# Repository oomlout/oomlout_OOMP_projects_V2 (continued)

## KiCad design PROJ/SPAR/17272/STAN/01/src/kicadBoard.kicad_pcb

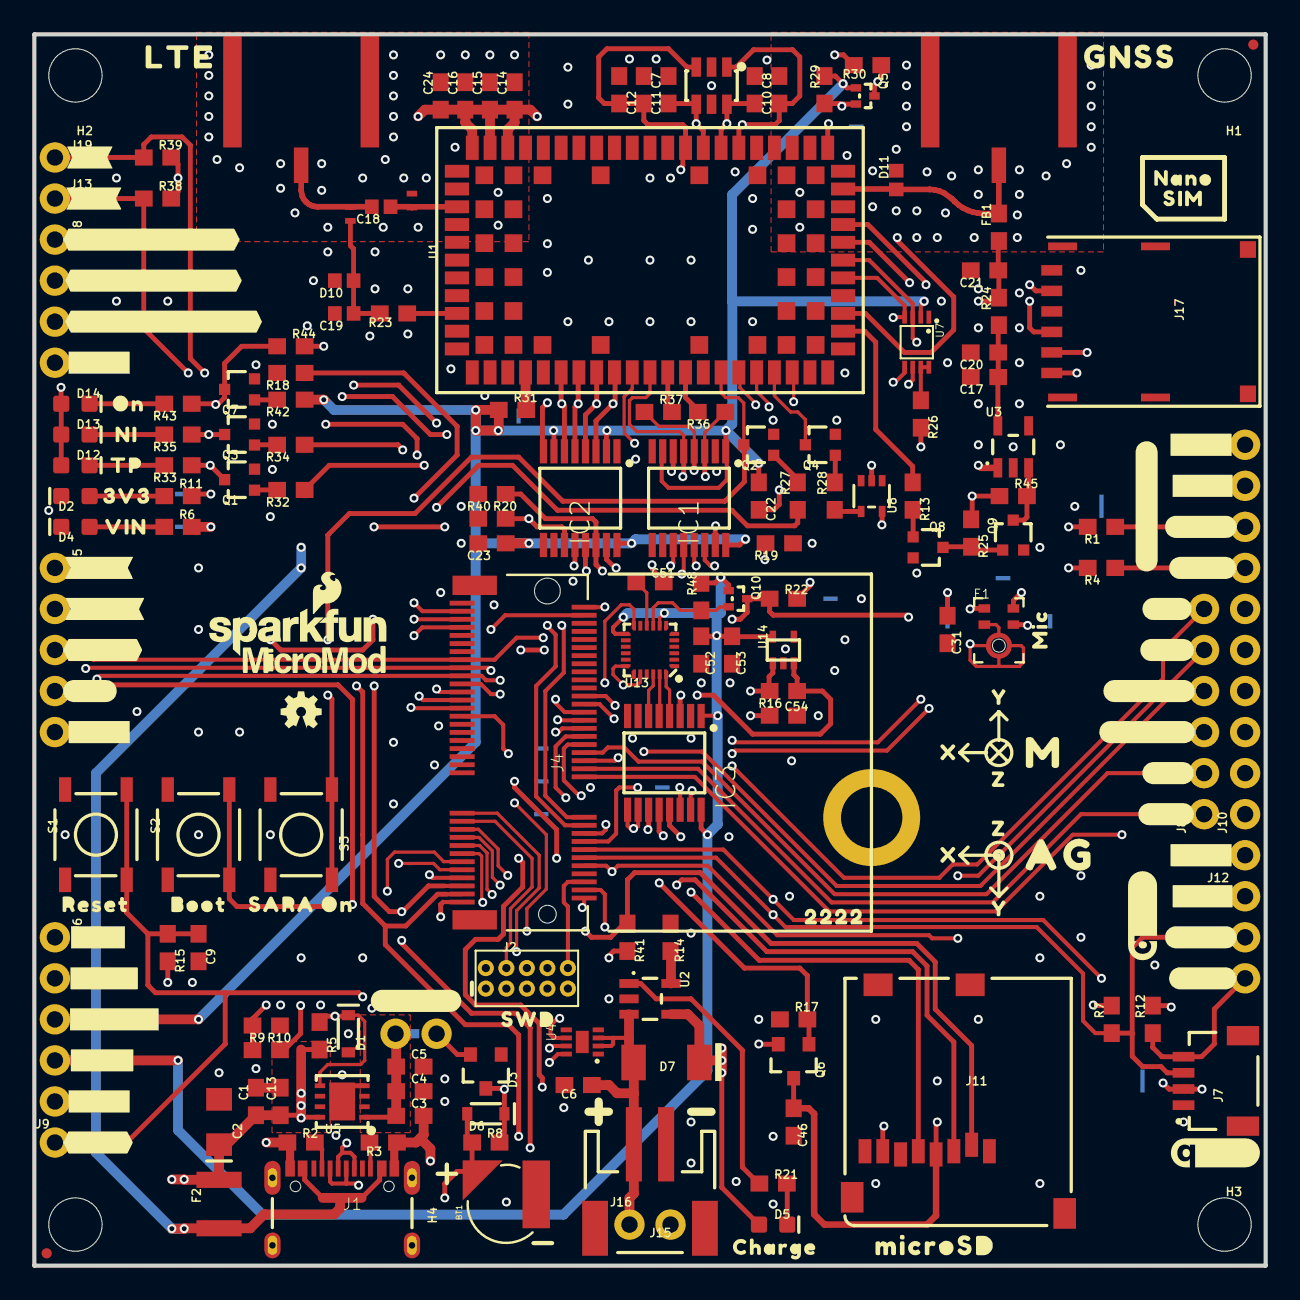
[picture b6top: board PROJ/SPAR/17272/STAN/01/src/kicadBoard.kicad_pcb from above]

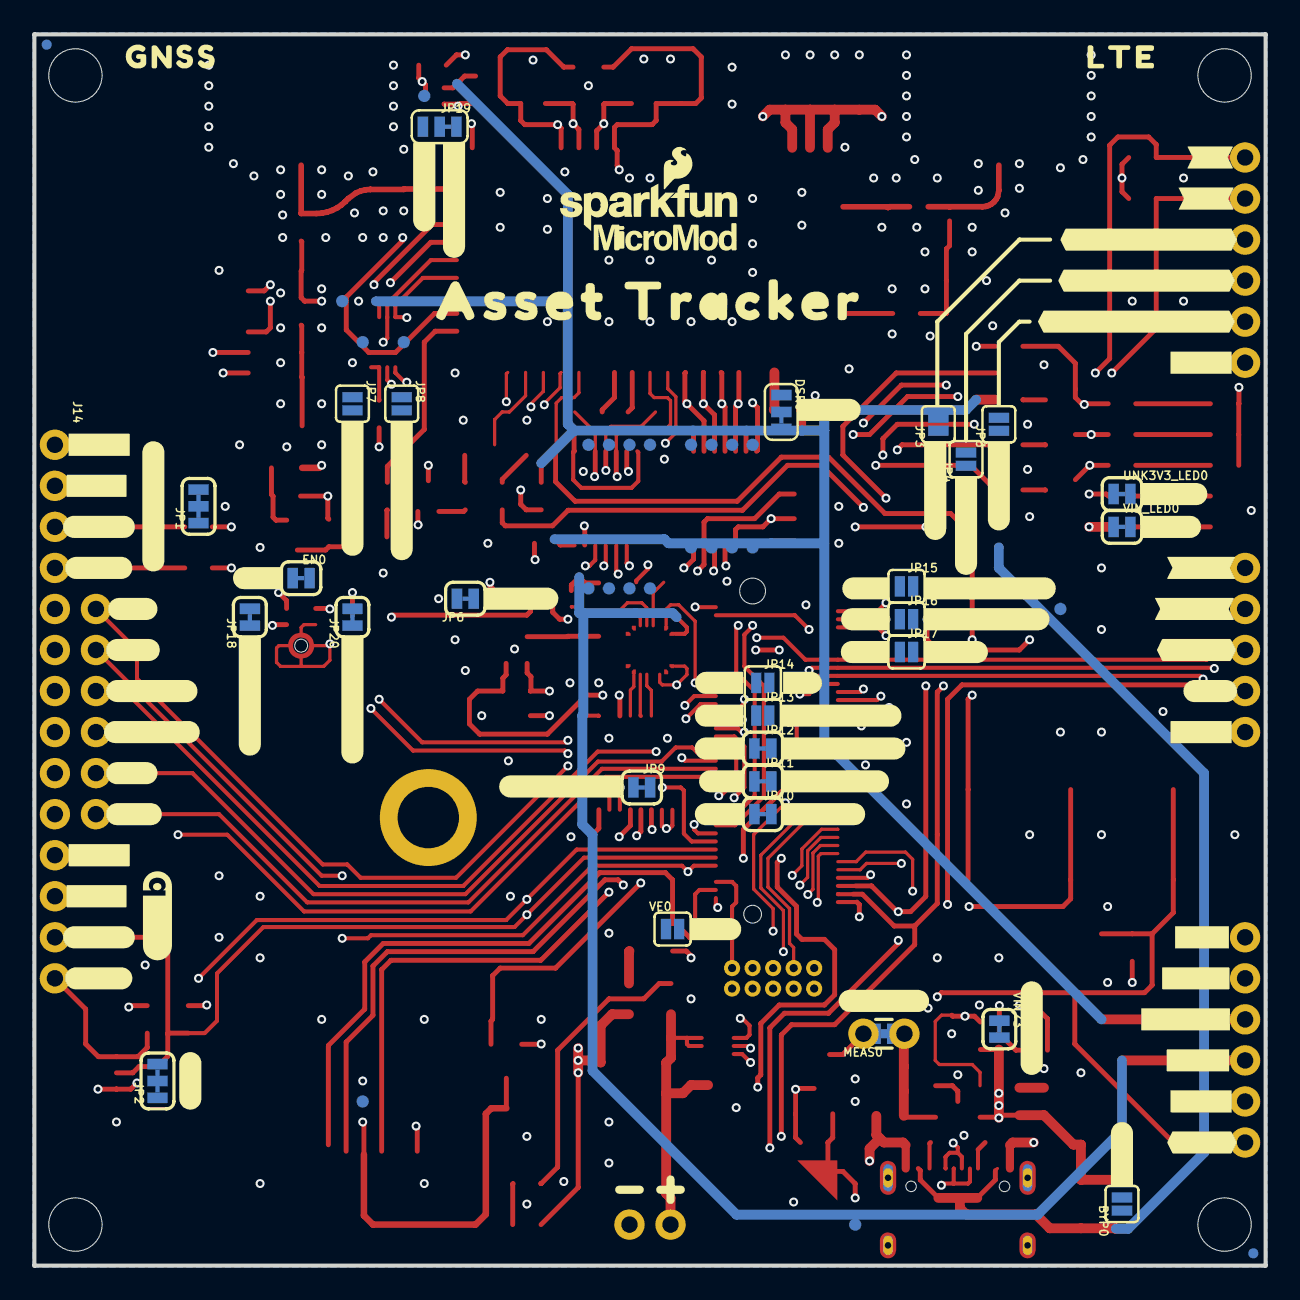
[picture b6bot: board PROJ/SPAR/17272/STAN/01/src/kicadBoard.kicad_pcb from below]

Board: 4 copper layers, 76.2 x 76.2 mm, 340 parts (128 on the bottom side), 137 nets.

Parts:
BT1: ML414H; ML414H_IV01E
BYP0: JUMPER-SMT_2_NO_SILK; SMT-JUMPER_2_NO_SILK
C1, C4, C12, C14, C20, C22, C23, C31, C46, C51, C52: 0.1uF; 0603
C2: 10uF; EIA3216
C3, C6: 4.7uF; 0603
C5, C13: 0.22uF; 0603
C7, C8, C10, C11, C21: 47pF; 0603
C9: 1nF; 0603
C15: 68pF; 0603
C16: 10uF; 0603
C17, C53, C54: 1.0uF; 0603
C18: 33pF; 0402
C19: 27pF; 0402
C24: 15pF; 0603
D1: 3.3V; SOD-323
D2: RED; LED-0603
D3: BAS70-05; SOT23-3
D4, D5: Yellow; LED-0603
D6: 3A/10V/280mV; SOD-323
D7: 1A/15V/220mV; DO-214BA
D8: DT1042-04SO-7; SOT23-6L
D10, D11: PESD0402; 0402
D12: GREEN; LED-0603
D13: BLUE; LED-0603
D14: WHITE; LED-0603
DSR0: JUMPER-SMT_3_1-NC_TRACE_SILK; SMT-JUMPER_3_1-NC_TRACE_SILK
E1: SPH0641LM4H-1; SPH0641LM4H-1_MICROPHONE
E3, E4: ANTENNA-SMA-GROUNDEDEDGE_SMA_SMD; SMA-EDGE-SMD
EN0: SMT-JUMPER_2_NC_TRACE_SILK
F2: 6V/2A; 1210
FB1: 30Ω/1.8A; 0603
FD1, FD2, FD3, FD4: FIDUCIALUFIDUCIAL; FIDUCIAL-MICRO
FRAME1, FRAME2: FRAME-LEDGER; CREATIVE_COMMONS
H1, H2, H3, H4: STAND-OFF
H5: STAND-OFF-REFLOW2.5MM_TALL; STAND-OFF-REFLOW-M2.5
IC1, IC2, IC3: SN74AVC4T774PW; SOP65P640X120-16N
J1: USB-C-16P_4LAYER-PADS
J2: JTAG; 2X5-PTH-1.27MM
J4: MICROMOD-2222-C; M.2-CONNECTOR-E
J5: SPI; 1X05_NO_SILK
J6: DIAG; 1X05_NO_SILK
J7: QWIIC_RIGHT_ANGLE; JST04_1MM_RA
J8, J10: 1X06_NO_SILK
J9: !RST!; 1X01_NO_SILK
J11: microSD; MICRO-SD-SOCKET
J12, J14: 1X04_NO_SILK
J13: TP; 1X01_NO_SILK
J15: JST-2-SMD
J16: 1X02_NO_SILK
J17: NANO_SIM; NANO_SIM_WURTH_693043020611
J18: SARA_USB; 1X04_NO_SILK
J19: NI; 1X01_NO_SILK
JP1, JP2: SMT-JUMPER_3_2-NC_TRACE_SILK
JP3, JP4, JP5, JP7, JP8, JP13, JP14, JP15, JP16, JP17: JUMPER-SMT_2_NO_SILK; SMT-JUMPER_2_NO_SILK
JP6, JP9, JP10, JP11, JP12, JP18, JP20: JUMPER-SMT_2_NC_TRACE_SILK; SMT-JUMPER_2_NC_TRACE_SILK
JP19: JUMPER-SMT_3_1-NC_TRACE_SILK; SMT-JUMPER_3_1-NC_TRACE_SILK
L1: DNP; 0402_COILCRAFT
L2: 68nH; 0402_COILCRAFT
LOGO1, LOGO4: SFE_LOGO_NAME_FLAME.1_INCH; SFE_LOGO_NAME_FLAME_.1
LOGO2, LOGO6, LOGO7: QWIIC_LOGO_CONNECTOR; QWIIC_5.5MM
LOGO3: OSHW-LOGOMINI; OSHW-LOGO-MINI
LOGO5: SPECIAL_INSTRUCTIONS-ORDERING; ORDERING_INSTRUCTIONS
MEAS0: COMBO-JUMPER_2_NC_TRACE
Q1, Q2, Q3, Q4, Q7, Q8, Q9: 310mA/60V/1.6Ω; SOT323
Q5, Q10: 20V/0.2A/8MHz/1.2Ω/1Vth; SOT-416FL
Q6: 20V/4.2A/52mΩ/1.4W; SOT23-3
R1, R4, R7, R12, R14, R22, R29, R30, R48: 2.2k; 0603
R2, R3: 5.1k; 0603
R5, R15, R16, R17, R18, R19, R20, R25, R38, R39, R40, R41, R44, R45: 100k; 0603
R6: 4.7k; 0603
R8: 3.3k; 0603
R9, R23: 10k; 0603
R10: 20k; 0603
R11, R13, R21, R27, R28, R32, R34, R42, R43: 1k; 0603
R24: 10; 0603
R26: 200k; 0603
R31, R36, R37: 0; 0603
R33: 100; 0603
R35: 470; 0603
S1: RESET; TACTILE_SWITCH_SMD_5.2MM
S2: BOOT; TACTILE_SWITCH_SMD_5.2MM
S3: SARA_PWR; TACTILE_SWITCH_SMD_5.2MM
TP1, TP2, TP3, TP4, TP5, TP6, TP7, TP8, TP9, TP10, TP12, TP13, TP14, TP15, TP16, TP17, TP18, TP19, TP20, TP21, TP22, TP23, TP24: TEST-POINT3; PAD.03X.03
U1: SARA-R510M8S; SARA-LGA
U2: MCP73831; SOT23-5
U3: 3.3V; SOT23-5
U4: MAX17048; DFN-8
U5: AP7361C-33FGE; UDFN-8
U7: PCA9306; VSSOP_8PIN
U8: 74HC1G04; SOT353
U13: 9DoF IMU; QFN24-3X3-ICM-20948
U14: 1.8V/100mA; SC70
U$1: #EN#0
U$2: MIC0
U$3, U$11, U$13, U$14: #3V3#1
U$4: #3V3#0
U$5, U$23: #SARA_I�C#0
U$6, U$7: #A0#5
U$8, U$9: #A1#4
U$10, U$25, U$35, U$68: #D0#1
U$12, U$15, U$16, U$22: #GND#0
U$17, U$86: #RST#1
U$18: #VE#0
U$19, U$87: #MEAS#2
U$20: #VIN#1
U$21: SWD0
U$24, U$34: MICROMOD_LOGO_.35
U$26, U$27, U$43, U$44: #SCL#3
U$28: MICROSD0
U$29, U$31: #D1#0
U$30, U$37, U$50, U$51: #SDA#2
U$32, U$41: #PWM0#3
U$33: #BYP#1
U$36: 3V37
U$38, U$48: Y2
U$39, U$47: X1
U$40: BOOT5
U$42, U$49: #PWM1#2
U$45: RESET6
U$46: VIN8
U$52, U$54: Z0
U$53: #I�C#0
U$55, U$56, U$73, U$74, U$81, U$82: #GND#4
U$57, U$58: #TP#0
U$59, U$60: #NI#0
U$61, U$62, U$63, U$64: #SARA_USB_D##0
U$65, U$66: #SARA_USB_DET#0
U$67, U$75: #VIN#0
U$69, U$70: #CIPO#2
U$71, U$72: #COPI#1
U$76, U$79: #3#3V#0
U$77, U$78: #SCK#0
U$80, U$83: #VCCIO#0
U$84, U$85: #1#8V#0
U$88, U$89: LTE0
U$90: NI0
U$91: TP0
U$92, U$93: #USB_D##0
U$94: #V_USB#0
U$95: AG0
U$96: M0
U$97: CHARGE0
U$98: ASSET_TRACKER0
U$99, U$100: GNSS0
U$101: ON0
U$102, U$105: #DSR#0
U$103: #SARA_INT#0
U$104: #RI#0
U$106: #SD_#CS##0
U$107: #IMU_PWR#0
U$108: #LTE_PWR#0
U$109: #SD_PWR#0
U$110: #SARA_#ON##0
U$111: #SARA_SCL#0
U$112: #SARA_SDA#0
U$113: SARA_ON0
U$114: #CIPO#0
U$115: 22220
U$116: #PDM_CLK#0
U$117: #PDM_DAT#0
U$118: #EXT_INT#0
U$119: #GPIO3#0
U$122: #G0#0
U$123: #G1#0
U$124: #G2#0
U$125: #G3#0
U$126: #G4#0
U$127: #G7#0
U$128: #G6#0
U$129: #G5#0
U$130: NANO0
U$131: SIM0
U$133: #VIN#3#0
U$134: #ICM_INT#0
UNK3V3_LED0: SMT-JUMPER_2_NC_TRACE_SILK
VE0: SMT-JUMPER_2_NO_SILK
VIN/3: JUMPER-SMT_2_NC_TRACE_SILK; SMT-JUMPER_2_NC_TRACE_SILK
VIN_LED0: SMT-JUMPER_2_NC_TRACE_SILK

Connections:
1.8V: C52.1, C53.1, IC3.1, IC3.16, J6.4, Q10.1, R48.2, U13.8, U13.13, U14.5
3.3V: C14.1, C15.1, C16.1, C24.1, C31.1, C54.1, D3.2, D12.A, D13.A, D14.A, EN0.2, IC1.15, IC2.15, IC3.15, J2.1, J4.2, J4.74, J6.2, J7.2, J12.2, J14.2, JP1.2, JP2.2, JP6.2, MEAS0.2, MEAS0.4, Q6.2, R15.2, R16.2, R25.1, R26.2, R30.2, R38.2, R39.2, R41.2, R44.2, R45.1, U1.51, U1.52, U1.53, U8.5, U14.1, UNK3V3_LED0.2
3.3V_EN: J4.4, VE0.1
A0: J4.34, J8.1
A1: J4.38, J8.2
ANT_GNSS_PWR_EN: R13.1, U1.23
ANT_REG_EN: Q9.3, R45.2, U3.3
CHG_LED: R21.1, U2.1
CTS1: IC1.12, J4.15, TP7.P$1
D0: J4.10, J5.4, J8.5
D1: J4.18, J8.6
DCD: IC2.13, J4.20, TP19.P$1
DSR: IC2.11, JP17.2, R20.2, TP21.P$1
DTR: IC2.14, J4.22, R40.1, TP18.P$1
G0: J4.40, JP10.1
G1: J4.42, JP11.1
G2: J4.44, JP12.1
G3: J4.46, JP13.1
G4: J4.48, JP14.1
G5: J4.73, JP15.1
G6: J4.71, JP16.1
G7: J4.69, JP17.1
GND: BT1.-, C1.2, C2.-, C3.2, C4.2, C5.2, C6.2, C7.2, C8.2, C9.2, C10.1, C11.1, C12.1, C13.2, C14.2, C15.2, C16.2, C17.2, C19.2, C20.2, C21.2, C22.2, C23.2, C24.2, C31.2, C46.2, C51.2, C52.2, C53.2, C54.2, D1.A, D2.C, D4.C, D8.2, D8.5, D10.2, D11.2, DSR0.1, E1.2, E1.3, E1.6, E1.7, E1.8, E3.GND@0, E3.GND@1, E4.GND@0, E4.GND@1, H5.1, IC1.2, IC1.8, IC1.9, IC1.10, IC2.1, IC2.9, IC2.10, IC3.2, IC3.7, IC3.8, IC3.9, IC3.10, J1.GND, J1.GND2, J2.3, J2.5, J2.9, J4.1, J4.7, J4.33, J4.36, J4.39, J4.45, J4.75, J5.5, J6.5, J7.1, J10.1, J10.2, J10.3, J10.4, J10.5, J10.6, J11.CD1, J11.GND, J11.GND1, J11.GND3, J12.1, J14.1, J15.1, J16.2, J17.C5, J18.4, L1.P$2, Q1.2, Q2.2, Q3.2, Q4.2, Q7.2, Q8.2, Q9.2, R2.1, R3.1, R9.1, R14.1, R17.1, R18.2, R19.1, R20.1, R40.2, S1.1, S1.2, S2.1, S2.2, S3.3, S3.4, U1.1, U1.3, U1.5, U1.14, U1.20, U1.21, U1.22, U1.30, U1.32, U1.43, U1.50, U1.54, U1.55, U1.57, U1.58, U1.59, U1.60, U1.61, U1.63, U1.64, U1.65, U1.66, U1.67, U1.68, U1.69, U1.70, U1.71, U1.72, U1.73, U1.74, U1.75, U1.76, U1.77, U1.78, U1.79, U1.80, U1.81, U1.82, U1.83, U1.84, U1.85, U1.86, U1.87, U1.88, U1.89, U1.90, U1.91, U1.92, U1.93, U1.94, U1.95, U1.96, U2.2, U3.2, U4.1, U4.4, U4.6, U4.9, U5.4, U5.EP, U7.P1, U8.3, U13.18, U13.20, U14.2
I2C_SCL: J4.14, J7.4, J12.4, R12.1, U4.7
I2C_SDA: J4.12, J7.3, J12.3, R7.1, U4.8
I2S_SCK/PDM_CLK: E1.4, JP18.2
I2S_WS/PDM_DAT: E1.1, JP20.2
ICM-20948-LV_INT: IC3.3, U13.12
ICM-20948-LV_SCK: IC3.5, U13.23
ICM-20948-LV_SDI: IC3.4, U13.24
ICM-20948-LV_SDO: Q10.2, R48.1, U13.9
ICM-20948-LV_~CS: IC3.6, U13.22
ICM_INT: IC3.14, JP9.1
ICM_PWR: JP13.2, R16.1, U14.3
ICM_~CS: IC3.11, J4.55
LTE_PWR_ON: JP12.2, R18.1, R27.1
MICROSD_PWR: JP11.2, Q6.1, R17.2
unnamed: R6.2, VIN_LED0.1
unnamed: JP1.3, R4.2
unnamed: JP1.1, R1.2
unnamed: E1.5, EN0.1
unnamed: J4.53, JP7.2
unnamed: R11.2, UNK3V3_LED0.1
unnamed: D2.A, R11.1
unnamed: D4.A, R6.1
unnamed: JP2.3, R12.2
unnamed: J1.A5, R2.2
unnamed: J1.B5, R3.2
unnamed: D1.C, R5.1, U5.5, VE0.2
unnamed: JP2.1, R7.2
unnamed: BT1.+, D6.A, R8.1, TP24.P$1
unnamed: C18.2, E3.SIG, L2.P$2
unnamed: C19.1, D10.1, L2.P$1, R23.2
unnamed: J4.51, JP8.2
unnamed: R10.2, VIN/3.1
unnamed: J4.16, JP9.2
unnamed: R14.2, U2.5
unnamed: D5.C, R21.2
unnamed: R26.1, U7.P7, U7.P8
unnamed: DSR0.2, IC2.8
unnamed: C17.1, C20.1, R24.1, U3.5
unnamed: C21.1, FB1.1, R24.2, TP22.P$1
unnamed: Q2.1, R27.2
unnamed: Q4.1, R28.2
unnamed: R28.1, U8.4
unnamed: JP6.1, R22.2
unnamed: C51.1, U13.10
unnamed: R31.2, U1.4
unnamed: Q1.1, R32.2
unnamed: J13.1, Q1.3, R33.1, R38.1
unnamed: D12.C, R33.2
unnamed: Q3.1, R34.2
unnamed: J19.1, Q3.3, R35.1, R39.1
unnamed: D13.C, R35.2
unnamed: R36.2, U1.13
unnamed: R37.2, U1.12
unnamed: Q8.1, R13.2
unnamed: Q8.3, Q9.1, R25.2
unnamed: JP19.2, Q5.2, R29.1
unnamed: Q7.1, R42.2
unnamed: D14.C, R43.2
unnamed: J4.52, JP20.1
unnamed: J4.50, JP18.1
PWM0: J4.32, J8.3
PWM1: J4.47, J8.4
RI: IC2.12, JP14.2, TP20.P$1
RTC_3V: D3.3, D6.C, J4.72, R8.2
RTS1: IC1.11, J4.13, R19.2, TP8.P$1
RX1: IC1.14, J4.19, TP5.P$1
SARA_ANT: C18.1, L1.P$1, U1.56
SARA_ANT_DET: R23.1, U1.62
SARA_ANT_GNSS: D11.1, E4.SIG, FB1.2, U1.31
SARA_CTS: IC1.5, TP3.P$1, U1.11
SARA_DCD/RXD2O: IC2.4, TP15.P$1, U1.8
SARA_DSR/RTS2I: IC2.6, TP17.P$1, U1.6
SARA_DTR/TXD2I: IC2.3, TP14.P$1, U1.9
SARA_EXT_INT: JP19.3, U1.33
SARA_GPIO3: JP19.1, U1.24
SARA_INT: JP15.2, Q5.3, R30.1, TP12.P$1
SARA_NI: R34.1, U1.16
SARA_PWR_ON: Q2.3, S3.1, S3.2, U1.15
SARA_RI/CTS2O: IC2.5, TP16.P$1, U1.7
SARA_RTS: IC1.6, TP4.P$1, U1.10
SARA_RXD: IC1.3, R36.1, TP1.P$1
SARA_SCL: J14.4, JP7.1, R4.1, U7.P6
SARA_SCL_1.8V: TP10.P$1, U1.27, U7.P3
SARA_SDA: J14.3, JP8.1, R1.1, U7.P5
SARA_SDA_1.8V: TP9.P$1, U1.26, U7.P4
SARA_TP: R32.1, U1.19
SARA_TXD: IC1.4, R37.1, TP2.P$1
SARA_USB_D+: J18.2, JP4.2, U1.29
SARA_USB_D-: J18.1, JP3.2, U1.28
SARA_VUSB_DET: J18.3, JP5.2, U1.17
SARA_~ON: JP16.2, Q7.3, R43.1, R44.1, TP13.P$1
SARA_~RESET: Q4.3, U1.18
SD_PWR: C46.1, J11.VCC, Q6.3, TP23.P$1
SD_~CS: J11.CS/DAT3, JP10.2, R41.1
SIM_CLK: C8.1, D8.1, J17.C3, U1.38
SIM_IO: C10.2, D8.6, J17.C7, U1.39
SIM_RST: C7.1, D8.4, J17.C2, U1.40
SPI_SCK: IC3.12, J4.57, J5.1, J11.SCLK
SPI_SDI: J4.61, J5.3, J11.DO/DAT0, Q10.3, R22.1
SPI_SDO: IC3.13, J4.59, J5.2, J11.DI/CMD
SWDCK: J2.4, J4.21
SWDIO: J2.2, J4.23
TX1: IC1.13, J4.17, TP6.P$1
USB_D+: J1.A6, J1.B6, J4.3, JP4.1
USB_D-: J1.A7, J1.B7, J4.5, JP3.1
VCCIO: C22.1, C23.1, DSR0.3, IC1.1, IC1.7, IC1.16, IC2.2, IC2.7, IC2.16, J6.3, Q5.1, R29.2, R31.1, R42.1, U7.P2
VIN: BYP0.2, C1.1, C2.+, C13.1, D5.A, D7.C, F2.2, J4.9, J6.1, R5.2, U2.4, U3.1, U5.8, VIN/3.2, VIN_LED0.2
VIN/3: J4.49, R9.2, R10.1
VREG_3.3V: C3.1, C4.1, C5.1, MEAS0.1, MEAS0.3, U5.1
VSIM: C11.2, C12.2, D8.3, J17.C1, U1.41
V_BATT: C6.1, D7.A, J15.2, J16.1, U2.3, U4.2, U4.3
V_USB: BYP0.1, F2.1, J1.VBUS1, J1.VBUS2, JP5.1
~BOOT: J4.11, S2.3, S2.4
~RESET: C9.1, J2.10, J4.6, J9.1, R15.1, S1.3, S1.4, U8.2

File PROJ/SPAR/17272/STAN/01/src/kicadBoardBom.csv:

"Id";"Designator";"Package";"Quantity";"Designation";"Supplier and ref";
1;"R33";"0603";1;"100";;;
2;"R44,R5,R16,R15,R38,R41,R40,R25,R17,R18,R39,R45,R20,R19";"0603";14;"100k";;;
3;"J12,J14";"1X04_NO_SILK";2;"";;;
4;"J5";"1X05_NO_SILK";1;"SPI";;;
5;"R3,R2";"0603";2;"5.1k";;;
6;"R8";"0603";1;"3.3k";;;
7;"R35";"0603";1;"470";;;
8;"R30,R1,R48,R4,R22,R7,R12,R14,R29";"0603";9;"2.2k";;;
9;"J9";"1X01_NO_SILK";1;"!RST!";;;
10;"U$90";"NI0";1;"";;;
11;"J17";"NANO_SIM_WURTH_693043020611";1;"NANO_SIM";;;
12;"J11";"MICRO-SD-SOCKET";1;"microSD";;;
13;"C10,C11,C7,C8,C21";"0603";5;"47pF";;;
14;"IC2,IC1,IC3";"SOP65P640X120-16N";3;"SN74AVC4T774PW";;;
15;"R34,R21,R28,R32,R27,R42,R13,R43,R11";"0603";9;"1k";;;
16;"H5";"STAND-OFF-REFLOW-M2.5";1;"STAND-OFF-REFLOW2.5MM_TALL";;;
17;"R26";"0603";1;"200k";;;
18;"U$28";"MICROSD0";1;"";;;
19;"U1";"SARA-LGA";1;"SARA-R510M8S";;;
20;"Q4,Q9,Q3,Q8,Q2,Q1,Q7";"SOT323";7;"310mA/60V/1.6Ω";;;
21;"U$15,U$12,U$16,U$22";"#GND#0";4;"";;;
22;"D3";"SOT23-3";1;"BAS70-05";;;
23;"U$81,U$73,U$56,U$74,U$82,U$55";"#GND#4";6;"";;;
24;"C3,C6";"0603";2;"4.7uF";;;
25;"U$8,U$9";"#A1#4";2;"";;;
26;"U$3,U$13,U$14,U$11";"#3V3#1";4;"";;;
27;"C18";"0402";1;"33pF";;;
28;"E1";"SPH0641LM4H-1_MICROPHONE";1;"SPH0641LM4H-1";;;
29;"D6";"SOD-323";1;"3A/10V/280mV";;;
30;"U$70,U$69";"#CIPO#2";2;"";;;
31;"U$131";"SIM0";1;"";;;
32;"U$88,U$89";"LTE0";2;"";;;
33;"U3";"SOT23-5";1;"3.3V";;;
34;"U$40";"BOOT5";1;"";;;
35;"U$17,U$86";"#RST#1";2;"";;;
36;"H1,H2,H3,H4";"STAND-OFF";4;"STAND-OFF";;;
37;"U$35,U$25,U$68,U$10";"#D0#1";4;"";;;
38;"U$36";"3V37";1;"";;;
39;"S3";"TACTILE_SWITCH_SMD_5.2MM";1;"SARA_PWR";;;
40;"J1";"USB-C-16P_4LAYER-PADS";1;"";;;
41;"U$115";"22220";1;"";;;
42;"J10,J8";"1X06_NO_SILK";2;"";;;
43;"D11,D10";"0402";2;"PESD0402";;;
44;"U$67,U$75";"#VIN#0";2;"";;;
45;"Q5,Q10";"SOT-416FL";2;"20V/0.2A/8MHz/1.2Ω/1Vth";;;
46;"U$61,U$63,U$62,U$64";"#SARA_USB_D##0";4;"";;;
47;"J13";"1X01_NO_SILK";1;"TP";;;
48;"C51,C23,C52,C20,C22,C1,C4,C46,C31,C14,C12";"0603";11;"0.1uF";;;
49;"U$39,U$47";"X1";2;"";;;
50;"U$80,U$83";"#VCCIO#0";2;"";;;
51;"U$101";"ON0";1;"";;;
52;"U13";"QFN24-3X3-ICM-20948";1;"9DoF IMU";;;
53;"U$91";"TP0";1;"";;;
54;"D5,D4";"LED-0603";2;"Yellow";;;
55;"U$2";"MIC0";1;"";;;
56;"R9,R23";"0603";2;"10k";;;
57;"LOGO6,LOGO2,LOGO7";"QWIIC_5.5MM";3;"QWIIC_LOGO_CONNECTOR";;;
58;"U$99,U$100";"GNSS0";2;"";;;
59;"U$130";"NANO0";1;"";;;
60;"C13,C5";"0603";2;"0.22uF";;;
61;"E3,E4";"SMA-EDGE-SMD";2;"ANTENNA-SMA-GROUNDEDEDGE_SMA_SMD";;;
62;"U$52,U$54";"Z0";2;"";;;
63;"J18";"1X04_NO_SILK";1;"SARA_USB";;;
64;"R37,R36,R31";"0603";3;"0";;;
65;"R6";"0603";1;"4.7k";;;
66;"LOGO5";"ORDERING_INSTRUCTIONS";1;"SPECIAL_INSTRUCTIONS-ORDERING";;;
67;"U$43,U$26,U$44,U$27";"#SCL#3";4;"";;;
68;"F2";"1210";1;"6V/2A";;;
69;"FRAME2,FRAME1";"CREATIVE_COMMONS";2;"FRAME-LEDGER";;;
70;"C54,C17,C53";"0603";3;"1.0uF";;;
71;"U$50,U$30,U$37,U$51";"#SDA#2";4;"";;;
72;"LOGO1,LOGO4";"SFE_LOGO_NAME_FLAME_.1";2;"SFE_LOGO_NAME_FLAME.1_INCH";;;
73;"U$5,U$23";"#SARA_I�C#0";2;"";;;
74;"C19";"0402";1;"27pF";;;
75;"U$65,U$66";"#SARA_USB_DET#0";2;"";;;
76;"J2";"2X5-PTH-1.27MM";1;"JTAG";;;
77;"FB1";"0603";1;"30Ω/1.8A";;;
78;"C9";"0603";1;"1nF";;;
79;"U$21";"SWD0";1;"";;;
80;"U7";"VSSOP_8PIN";1;"PCA9306";;;
81;"U$6,U$7";"#A0#5";2;"";;;
82;"U$84,U$85";"#1#8V#0";2;"";;;
83;"FD1,FD2,FD3,FD4";"FIDUCIAL-MICRO";4;"FIDUCIALUFIDUCIAL";;;
84;"J4";"M.2-CONNECTOR-E";1;"MICROMOD-2222-C";;;
85;"U8";"SOT353";1;"74HC1G04";;;
86;"Q6";"SOT23-3";1;"20V/4.2A/52mΩ/1.4W";;;
87;"U$57,U$58";"#TP#0";2;"";;;
88;"D14";"LED-0603";1;"WHITE";;;
89;"U$96";"M0";1;"";;;
90;"D1";"SOD-323";1;"3.3V";;;
91;"S1";"TACTILE_SWITCH_SMD_5.2MM";1;"RESET";;;
92;"C15";"0603";1;"68pF";;;
93;"U$59,U$60";"#NI#0";2;"";;;
94;"L1";"0402_COILCRAFT";1;"DNP";;;
95;"U$32,U$41";"#PWM0#3";2;"";;;
96;"U$24,U$34";"MICROMOD_LOGO_.35";2;"";;;
97;"C16";"0603";1;"10uF";;;
98;"J7";"JST04_1MM_RA";1;"QWIIC_RIGHT_ANGLE";;;
99;"U5";"UDFN-8";1;"AP7361C-33FGE";;;
100;"J16";"1X02_NO_SILK";1;"";;;
101;"S2";"TACTILE_SWITCH_SMD_5.2MM";1;"BOOT";;;
102;"U$48,U$38";"Y2";2;"";;;
103;"U$95";"AG0";1;"";;;
104;"U$71,U$72";"#COPI#1";2;"";;;
105;"LOGO3";"OSHW-LOGO-MINI";1;"OSHW-LOGOMINI";;;
106;"C24";"0603";1;"15pF";;;
107;"U14";"SC70";1;"1.8V/100mA";;;
108;"U$29,U$31";"#D1#0";2;"";;;
109;"D7";"DO-214BA";1;"1A/15V/220mV";;;
110;"U$77,U$78";"#SCK#0";2;"";;;
111;"U$46";"VIN8";1;"";;;
112;"J19";"1X01_NO_SILK";1;"NI";;;
113;"U$45";"RESET6";1;"";;;
114;"D13";"LED-0603";1;"BLUE";;;
115;"L2";"0402_COILCRAFT";1;"68nH";;;
116;"J15";"JST-2-SMD";1;"";;;
117;"BT1";"ML414H_IV01E";1;"ML414H";;;
118;"U2";"SOT23-5";1;"MCP73831";;;
119;"C2";"EIA3216";1;"10uF";;;
120;"U$97";"CHARGE0";1;"";;;
121;"U4";"DFN-8";1;"MAX17048";;;
122;"R24";"0603";1;"10";;;
123;"U$76,U$79";"#3#3V#0";2;"";;;
124;"U$42,U$49";"#PWM1#2";2;"";;;
125;"D12";"LED-0603";1;"GREEN";;;
126;"U$113";"SARA_ON0";1;"";;;
127;"D2";"LED-0603";1;"RED";;;
128;"D8";"SOT23-6L";1;"DT1042-04SO-7";;;
129;"U$19,U$87";"#MEAS#2";2;"";;;
130;"J6";"1X05_NO_SILK";1;"DIAG";;;
131;"R10";"0603";1;"20k";;;
132;"JP19,DSR0";"SMT-JUMPER_3_1-NC_TRACE_SILK";2;"JUMPER-SMT_3_1-NC_TRACE_SILK";;;
133;"U$122";"#G0#0";1;"";;;
134;"U$116";"#PDM_CLK#0";1;"";;;
135;"JP5,JP17,JP4,JP15,JP8,JP3,JP7,BYP0,JP16,JP14,JP13";"SMT-JUMPER_2_NO_SILK";11;"JUMPER-SMT_2_NO_SILK";;;
136;"TP14,TP19,TP15,TP23,TP8,TP3,TP21,TP12,TP24,TP6,TP10,TP2,TP18,TP13,TP4,TP16,TP9,TP1,TP20,TP7,TP17,TP5,TP22";"PAD.03X.03";23;"TEST-POINT3";;;
137;"JP9,JP6,JP20,JP18,JP10,VIN/3,JP11,JP12";"SMT-JUMPER_2_NC_TRACE_SILK";8;"JUMPER-SMT_2_NC_TRACE_SILK";;;
138;"VE0";"SMT-JUMPER_2_NO_SILK";1;"";;;
139;"U$92,U$93";"#USB_D##0";2;"";;;
140;"U$102,U$105";"#DSR#0";2;"";;;
141;"U$128";"#G6#0";1;"";;;
142;"U$126";"#G4#0";1;"";;;
143;"U$127";"#G7#0";1;"";;;
144;"EN0,UNK3V3_LED0,VIN_LED0";"SMT-JUMPER_2_NC_TRACE_SILK";3;"";;;
145;"U$125";"#G3#0";1;"";;;
146;"U$133";"#VIN#3#0";1;"";;;
147;"U$18";"#VE#0";1;"";;;
148;"U$53";"#I�C#0";1;"";;;
149;"U$114";"#CIPO#0";1;"";;;
150;"U$103";"#SARA_INT#0";1;"";;;
151;"MEAS0";"COMBO-JUMPER_2_NC_TRACE";1;"";;;
152;"U$94";"#V_USB#0";1;"";;;
153;"U$33";"#BYP#1";1;"";;;
154;"JP2,JP1";"SMT-JUMPER_3_2-NC_TRACE_SILK";2;"";;;
155;"U$4";"#3V3#0";1;"";;;
156;"U$123";"#G1#0";1;"";;;
157;"U$20";"#VIN#1";1;"";;;
158;"U$134";"#ICM_INT#0";1;"";;;
159;"U$1";"#EN#0";1;"";;;
160;"U$98";"ASSET_TRACKER0";1;"";;;
161;"U$129";"#G5#0";1;"";;;
162;"U$109";"#SD_PWR#0";1;"";;;
163;"U$104";"#RI#0";1;"";;;
164;"U$108";"#LTE_PWR#0";1;"";;;
165;"U$107";"#IMU_PWR#0";1;"";;;
166;"U$118";"#EXT_INT#0";1;"";;;
167;"U$111";"#SARA_SCL#0";1;"";;;
168;"U$110";"#SARA_#ON##0";1;"";;;
169;"U$124";"#G2#0";1;"";;;
170;"U$119";"#GPIO3#0";1;"";;;
171;"U$117";"#PDM_DAT#0";1;"";;;
172;"U$106";"#SD_#CS##0";1;"";;;
173;"U$112";"#SARA_SDA#0";1;"";;;

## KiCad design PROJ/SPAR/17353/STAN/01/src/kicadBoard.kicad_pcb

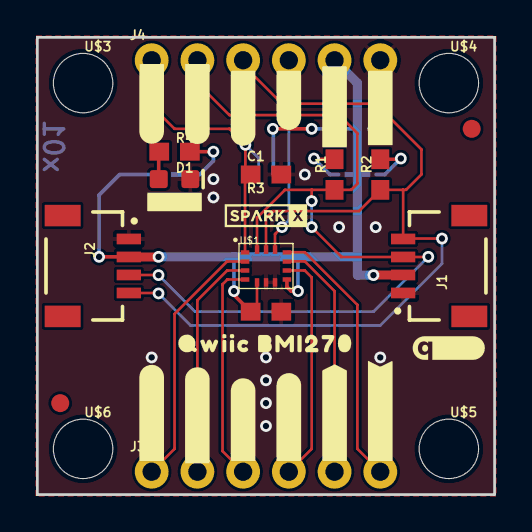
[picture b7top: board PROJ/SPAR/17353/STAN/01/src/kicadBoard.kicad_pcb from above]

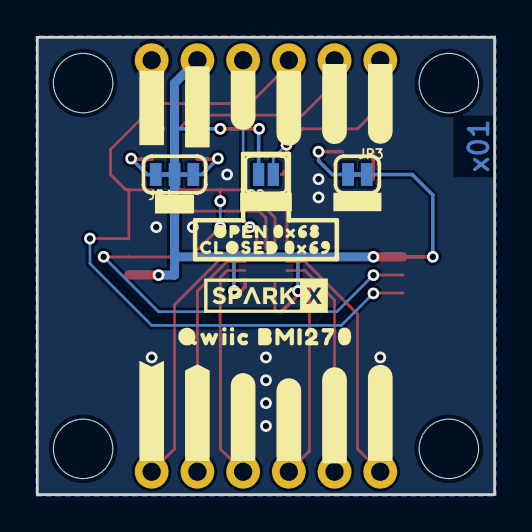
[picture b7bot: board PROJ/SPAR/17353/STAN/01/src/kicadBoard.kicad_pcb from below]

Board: 2 copper layers, 25.4 x 25.4 mm, 56 parts (22 on the bottom side), 16 nets.

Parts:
C1: 0.1uF; 0603
D1: RED; LED-0603
FD1, FD2: FIDUCIAL1X2; FIDUCIAL-1X2
FRAME1: FRAME-LETTERNO_PACKAGE; DUMMY
J1, J2: QWIIC_RIGHT_ANGLE; JST04_1MM_RA
J3, J4: 1X06_NO_SILK
JP1: JUMPER-SMT_3_2-NC_TRACE_SILK; SMT-JUMPER_3_2-NC_TRACE_SILK
JP2: JUMPER-SMT_2_NO_SILK; SMT-JUMPER_2_NO_SILK
JP3: JUMPER-SMT_2_NC_TRACE_SILK; SMT-JUMPER_2_NC_TRACE_SILK
R1, R2: 2.2k; 0603
R3: 10k; 0603
R4: 1k; 0603
U$1: BMI270
U$2, U$35: #3#3V_#4
U$3, U$4, U$5, U$6: STAND-OFF
U$7, U$34: #GND_#4
U$8, U$36: #CS_#3
U$9, U$37: #SCL_#2
U$10, U$38: #SDA_#1
U$11, U$39: #SDO_#0
U$12, U$28: #_OSDO#8
U$13, U$29: #_OCSB#7
U$14, U$31: #_INT1#7
U$15, U$30: #_INT2#7
U$16, U$32: #_ASCX#5
U$17, U$33: #_ASDX#6
U$18: #PWR#2711
U$19, U$26: QWIIC_BMI2709
U$20: SPARKX-TINY
U$21: #I�C#2714
U$22: #LED#2712
U$23: #ADR#2713
U$24: OPEN_0X682714
U$25: CLOSED_0X692714
U$27: SPARKX-SMALL
U$41: QWIIC_4MM

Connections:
3.3V: C1.2, J1.2, J2.2, J4.5, JP1.2, JP2.2, JP3.2, U$1.5, U$1.8
ADDR_SEL: J4.1, JP2.1, R3.2, U$1.1
ASCX: J3.2, U$1.3
ASDX: J3.1, U$1.2
CS: J4.4, U$1.12
GND: C1.1, D1.C, J1.1, J2.1, J4.6, R3.1, U$1.6, U$1.7
INT1: J3.3, U$1.4
INT2: J3.4, U$1.9
unnamed: JP1.1, R1.2
unnamed: JP1.3, R2.2
unnamed: JP3.1, R4.2
unnamed: D1.A, R4.1
OCSB: J3.5, U$1.10
OSDO: J3.6, U$1.11
SCL: J1.4, J2.4, J4.3, R2.1, U$1.13
SDA: J1.3, J2.3, J4.2, R1.1, U$1.14

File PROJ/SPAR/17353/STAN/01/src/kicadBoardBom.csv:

"Id";"Designator";"Package";"Quantity";"Designation";"Supplier and ref";
1;"U$16,U$32";"#_ASCX#5";2;"";;;
2;"U$10,U$38";"#SDA_#1";2;"";;;
3;"U$12,U$28";"#_OSDO#8";2;"";;;
4;"U$11,U$39";"#SDO_#0";2;"";;;
5;"FD2,FD1";"FIDUCIAL-1X2";2;"FIDUCIAL1X2";;;
6;"C1";"0603";1;"0.1uF";;;
7;"U$9,U$37";"#SCL_#2";2;"";;;
8;"U$8,U$36";"#CS_#3";2;"";;;
9;"R2,R1";"0603";2;"2.2k";;;
10;"U$20";"SPARKX-TINY";1;"";;;
11;"U$7,U$34";"#GND_#4";2;"";;;
12;"U$5,U$6,U$4,U$3";"STAND-OFF";4;"";;;
13;"U$1";"BMI270";1;"BMI270";;;
14;"J1,J2";"JST04_1MM_RA";2;"QWIIC_RIGHT_ANGLE";;;
15;"U$15,U$30";"#_INT2#7";2;"";;;
16;"R3";"0603";1;"10k";;;
17;"U$19,U$26";"QWIIC_BMI2709";2;"";;;
18;"U$13,U$29";"#_OCSB#7";2;"";;;
19;"D1";"LED-0603";1;"RED";;;
20;"J3,J4";"1X06_NO_SILK";2;"";;;
21;"U$17,U$33";"#_ASDX#6";2;"";;;
22;"U$18";"#PWR#2711";1;"";;;
23;"R4";"0603";1;"1k";;;
24;"U$14,U$31";"#_INT1#7";2;"";;;
25;"U$2,U$35";"#3#3V_#4";2;"";;;
26;"U$41";"QWIIC_4MM";1;"";;;
27;"FRAME1";"DUMMY";1;"FRAME-LETTERNO_PACKAGE";;;
28;"JP1";"SMT-JUMPER_3_2-NC_TRACE_SILK";1;"JUMPER-SMT_3_2-NC_TRACE_SILK";;;
29;"JP2";"SMT-JUMPER_2_NO_SILK";1;"JUMPER-SMT_2_NO_SILK";;;
30;"U$24";"OPEN_0X682714";1;"";;;
31;"JP3";"SMT-JUMPER_2_NC_TRACE_SILK";1;"JUMPER-SMT_2_NC_TRACE_SILK";;;
32;"U$27";"SPARKX-SMALL";1;"";;;
33;"U$25";"CLOSED_0X692714";1;"";;;
34;"U$21";"#I�C#2714";1;"";;;
35;"U$22";"#LED#2712";1;"";;;
36;"U$23";"#ADR#2713";1;"";;;
